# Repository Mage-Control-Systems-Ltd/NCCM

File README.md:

# Net Class Clearance Matrix (NCCM) KiCad Plugin

Net class clearance matrix plugin for KiCad! To generate custom rules for clearances between net classes through a matrix GUI.

## Installing
### Via KiCad's Plugin and Content Manager
Search 'NCCM' in KiCad's PCM and it should show up! Select 'Yes' when prompted to enable KiCad's Plugin API.

### Manual
To install place this entire folder in the platform-dependent plugins directory,

| Platform | Path
|----------|------
| Windows  | `C:\Users\<username>\Documents\KiCad\9.0\plugins`
| macOS    | `/Users/<username>/Documents/KiCad/9.0/plugins`
| Linux    | `~/.local/share/KiCad/9.0/plugins`

Then in KiCad preferences go to `Plugins`, check the `Enable KiCad API` checkbox.

Restart KiCad and it should appear in the layout editor on the top right.

## Using
On succesful installation, open KiCad and you should see the NCCM logo on the toolbar. Once clicked you should see this simple GUI populated with all your project net classes.

Enter your net class clearances and click `Update Custom Rules` to add them to the `.kicad_dru` file. Remove the custom rules by clicking `Remove From Custom Rules`.

## Development
GUI was built using wxFormBuilder. Project file for that is under `ui/`.

The `kicad-python` package was installed and used as specified in the KiCad API Python Bindings [repository](https://gitlab.com/kicad/code/kicad-python).

To debug the plugin with a KiCad instance open in your own terminal, enable the KiCad API by checking the `Enable KiCad API` checkbox. It will default to the Python interpreter shipped with KiCad but that can be changed if desired.

For live debugging a board file must be loaded to get data from. Feel free to use the test project under `tests/`.

## Known Issues
The plugin might not work if there are multiple instances of KiCad open. This is possibly a limitation of `kicad-python`.

## License
NCCM is licensed under the GNU General Public License v3.0 (GPLv3). It incorporates components that are licensed under the MIT License. These MIT-licensed modules remain under their original license terms and are compatible with the GPLv3. For full licensing details, refer to the LICENSE file and visit https://www.gnu.org/licenses/gpl-3.0.html.

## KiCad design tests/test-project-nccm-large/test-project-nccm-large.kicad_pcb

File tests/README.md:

# NCCM Tests
Run `pytest` from this directory to execute the tests. Please remember to open the test-project-nccm.kicad_pcb before running the tests since the KiCAD Plugin API attaches to a running KiCAD instance.

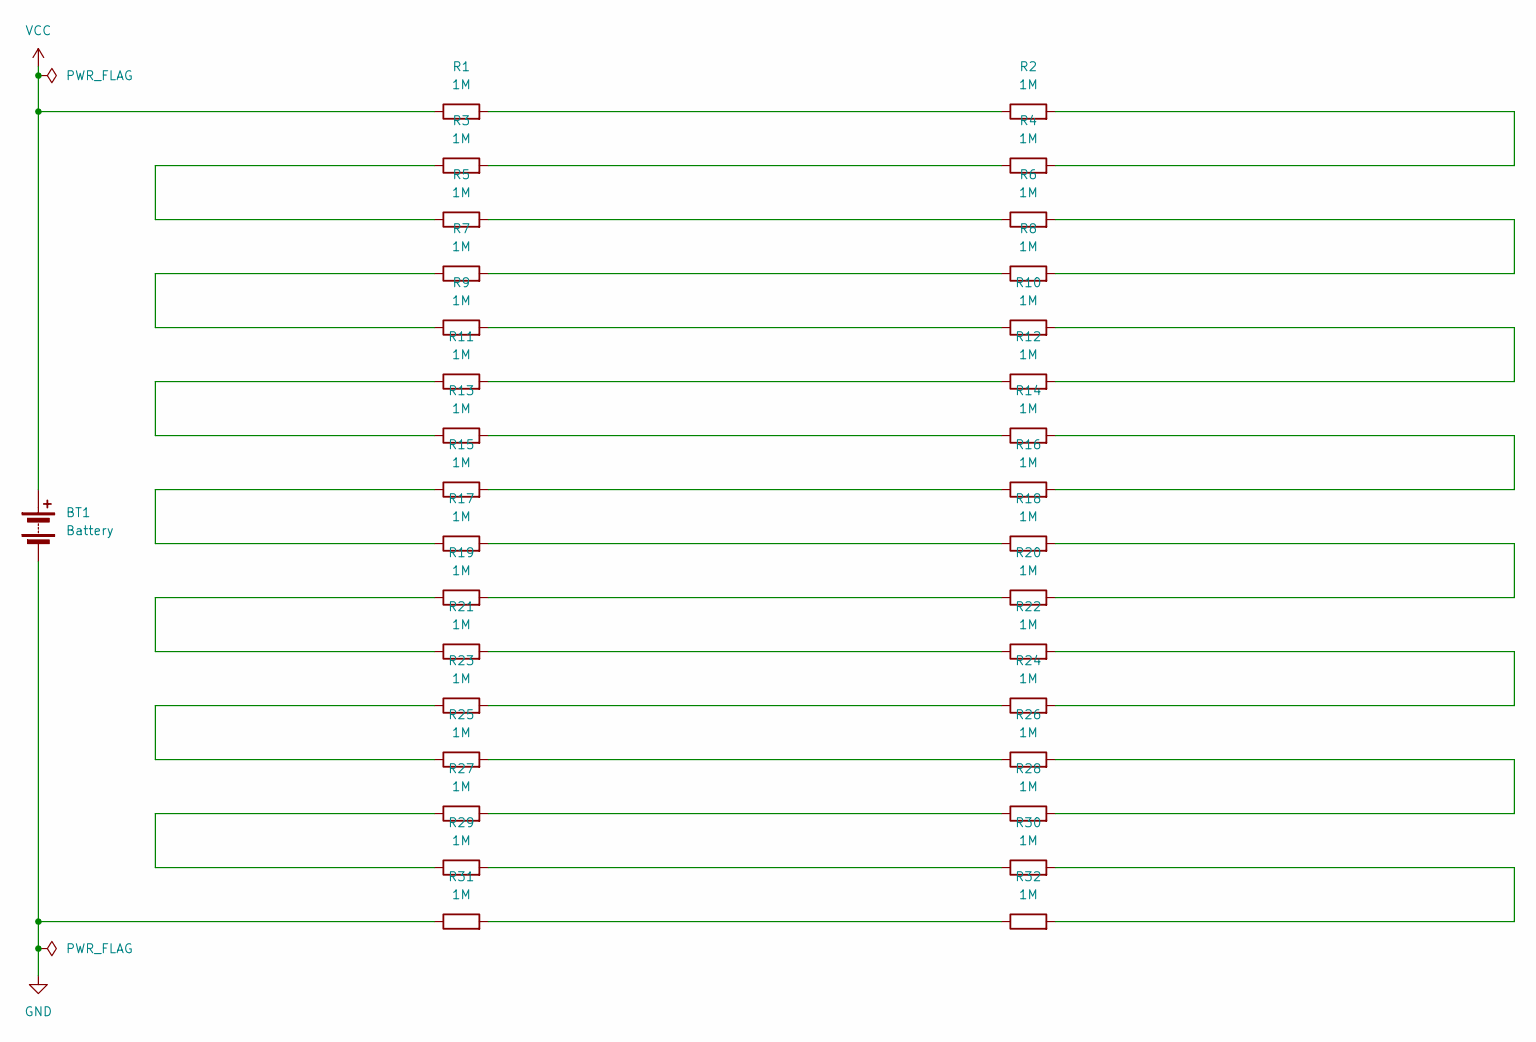
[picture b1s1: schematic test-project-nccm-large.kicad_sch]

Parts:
BT1: Battery; BatteryHolder_Keystone_2466_1xAAA
R1, R2, R3, R4, R5, R6, R7, R8, R9, R10, R11, R12, R13, R14, R15, R16, R17, R18, R19, R20, R21, R22, R23, R24, R25, R26, R27, R28, R29, R30, R31, R32: 1M; R_Axial_DIN0204_L3.6mm_D1.6mm_P7.62mm_Horizontal

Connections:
GND: BT1.2 (-), R31.1
unnamed: R1.2, R2.1
unnamed: R2.2, R4.2
unnamed: R3.1, R5.1
unnamed: R3.2, R4.1
unnamed: R5.2, R6.1
unnamed: R6.2, R8.2
unnamed: R7.1, R9.1
unnamed: R7.2, R8.1
unnamed: R9.2, R10.1
unnamed: R10.2, R12.2
unnamed: R11.1, R13.1
unnamed: R11.2, R12.1
unnamed: R13.2, R14.1
unnamed: R14.2, R16.2
unnamed: R15.1, R17.1
unnamed: R15.2, R16.1
unnamed: R17.2, R18.1
unnamed: R18.2, R20.2
unnamed: R19.1, R21.1
unnamed: R19.2, R20.1
unnamed: R21.2, R22.1
unnamed: R22.2, R24.2
unnamed: R23.1, R25.1
unnamed: R23.2, R24.1
unnamed: R25.2, R26.1
unnamed: R26.2, R28.2
unnamed: R27.1, R29.1
unnamed: R27.2, R28.1
unnamed: R29.2, R30.1
unnamed: R30.2, R32.2
unnamed: R31.2, R32.1
VCC: BT1.1 (+), R1.1

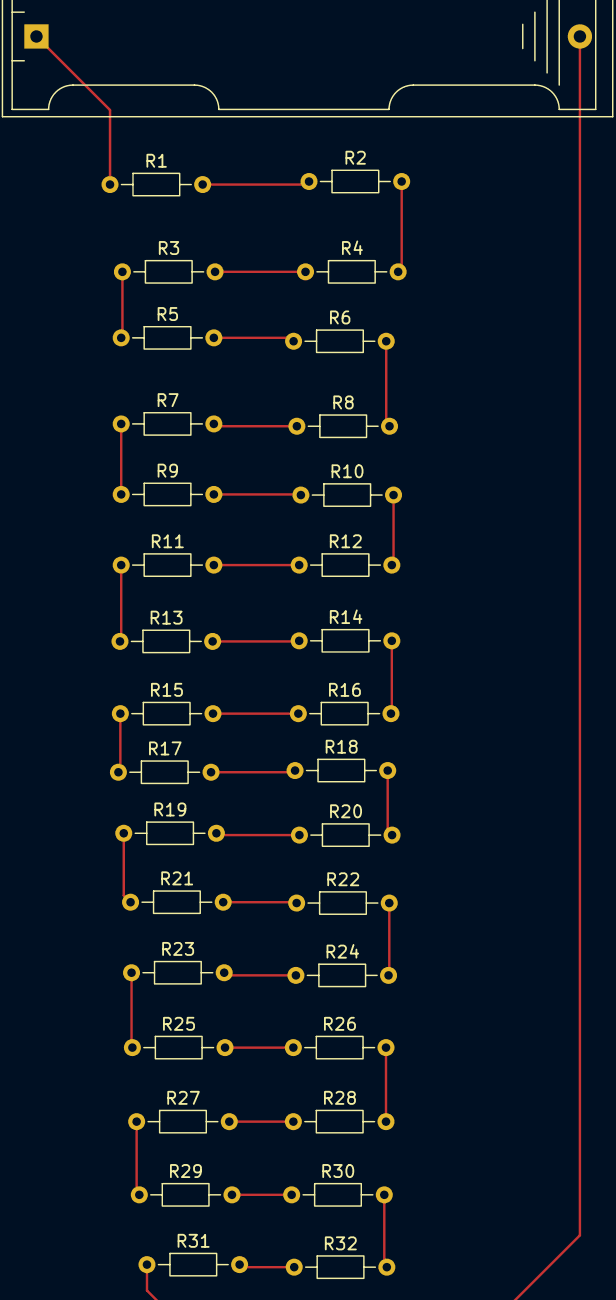
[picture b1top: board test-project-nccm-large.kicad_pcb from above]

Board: 2 copper layers, 33 parts (0 on the bottom side), 33 nets.

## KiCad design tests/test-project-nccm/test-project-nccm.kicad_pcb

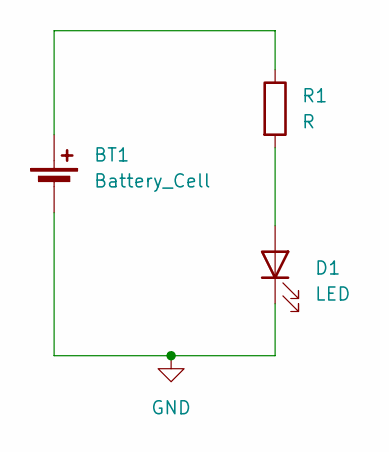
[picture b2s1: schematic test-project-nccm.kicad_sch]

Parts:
BT1: Battery_Cell; BatteryHolder_Bulgin_BX0034_1xAAA
D1: LED; LED_D1.8mm_W1.8mm_H2.4mm_Horizontal_O1.27mm_Z1.6mm
R1: R; R_Axial_DIN0204_L3.6mm_D1.6mm_P7.62mm_Horizontal

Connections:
GND: BT1.2 (-), D1.1 (K)
unnamed: BT1.1 (+), R1.1
unnamed: D1.2 (A), R1.2

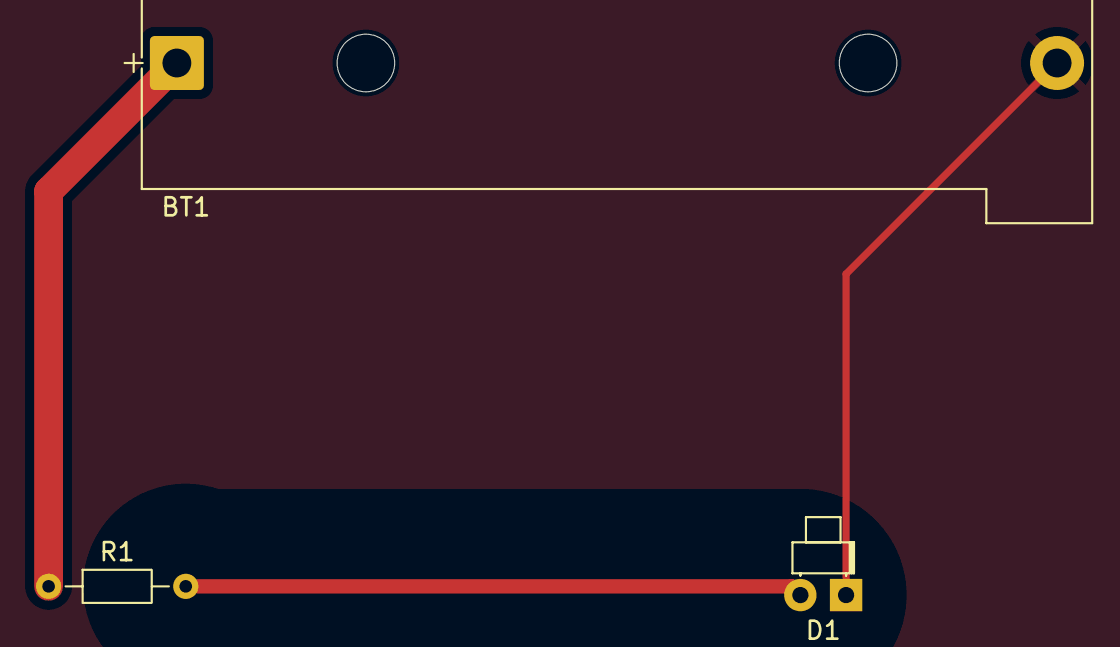
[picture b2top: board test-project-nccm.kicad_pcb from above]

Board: 2 copper layers, 3 parts (0 on the bottom side), 3 nets.

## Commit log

2025-10-08 Initial commit.
2025-10-09 fix: Long net class names were being cut off by row/col label size.
2025-10-09 add: Tests for new long net class name.
2025-10-09 fix: Updated __version__.
2025-10-15 Updated README issue link.
2025-10-23 Fixed metadata.json.
2025-10-27 Updated README with PCM info.
2025-11-12 fix(dialog): Fix dialog not showing for large net class amount (#2)
    Set the grid to a max size but still allowing the window to
    auto-resize based on content. This makes the grid scroll-able
    and therefore more useable for large net class amounts.
2025-11-12 Version bump
